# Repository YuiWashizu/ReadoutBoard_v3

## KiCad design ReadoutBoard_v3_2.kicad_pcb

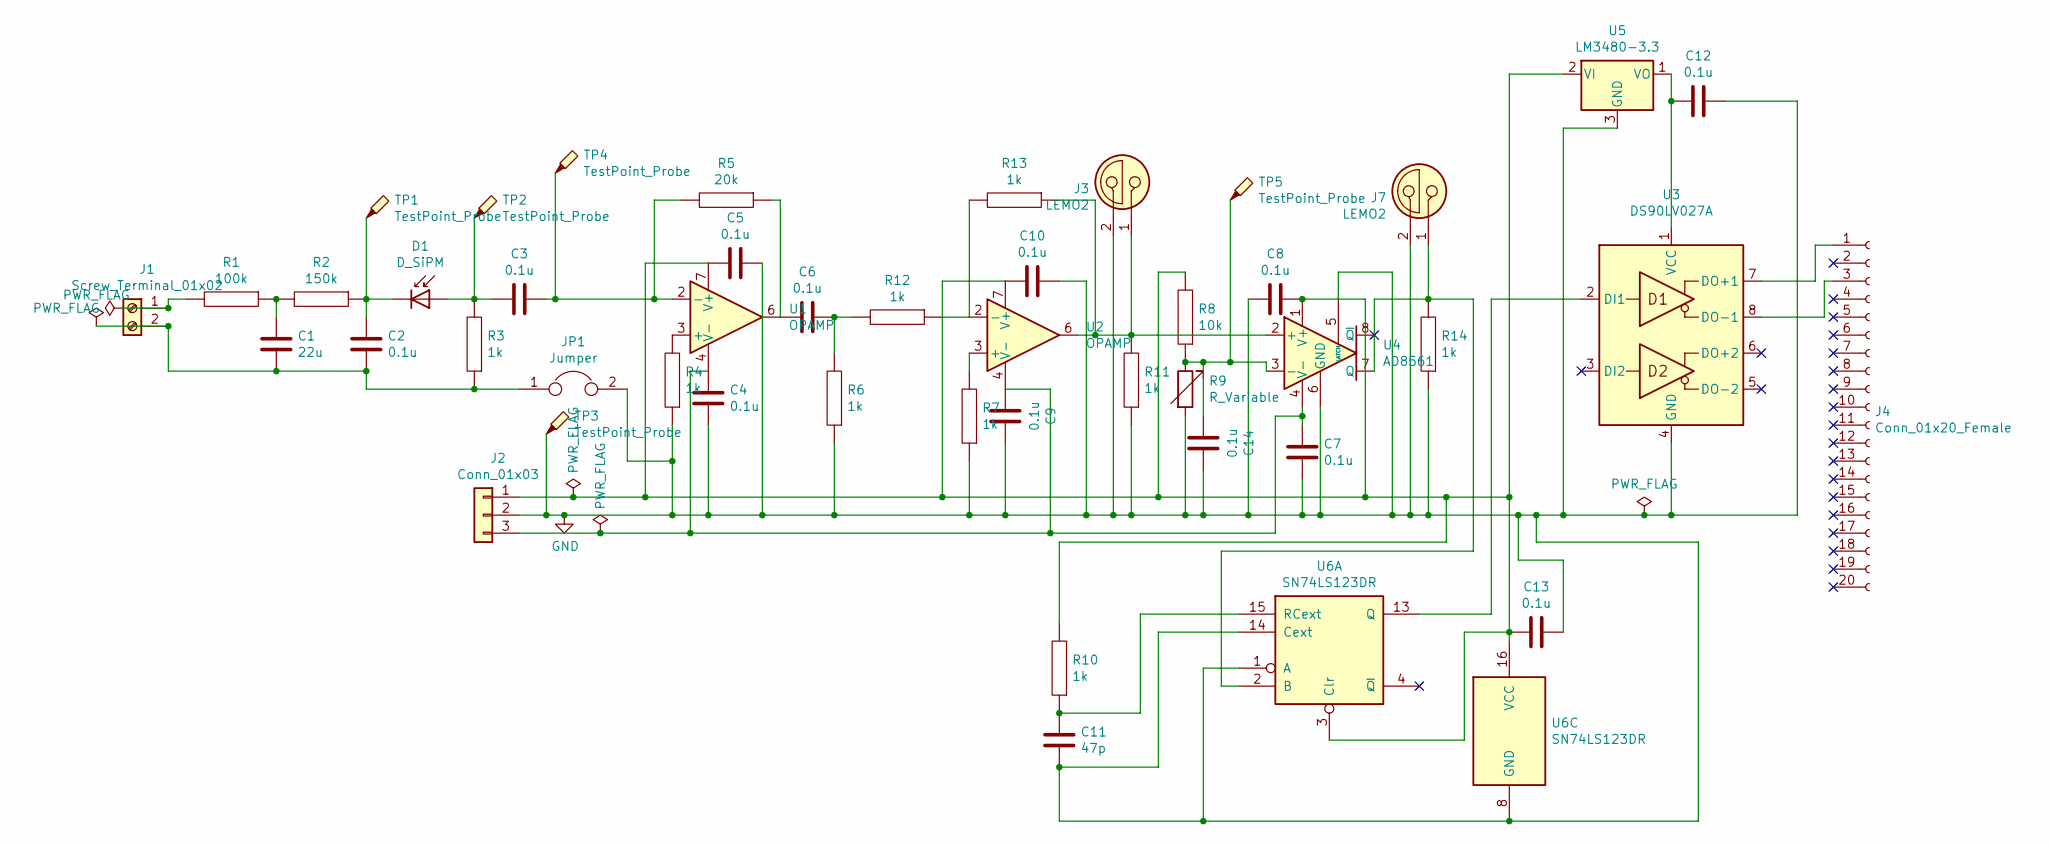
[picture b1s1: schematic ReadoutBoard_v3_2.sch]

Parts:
C1: 22u; PinHeader_1x02_P2.54mm_Vertical
C2, C3, C4, C5, C6, C7, C8, C9, C10, C12, C13, C14: 0.1u; C_0603_1608Metric
C11: 47p; C_0603_1608Metric
D1: D_SiPM; PinHeader_1x02_P2.54mm_Vertical
J1: Screw_Terminal_01x02; TerminalBlock_bornier-2_P5.08mm
J2: Conn_01x03; FanPinHeader_1x03_P2.54mm_Vertical
J3, J7: LEMO2; SMA_Amphenol_132134-16_Vertical
J4: Conn_01x20_Female; DisplayPort
JP1: Jumper; PinHeader_1x02_P2.54mm_Vertical
R1: 100k; R_0402_1005Metric
R2: 150k; R_0402_1005Metric
R3, R4, R6, R7, R10, R11, R12, R13, R14: 1k; R_0402_1005Metric
R5: 20k; R_0402_1005Metric
R8: 10k; R_0402_1005Metric
R9: R_Variable; PinHeader_1x03_P2.54mm_Vertical
TP1, TP2, TP3, TP4, TP5: TestPoint_Probe; TestPoint_Loop_D2.50mm_Drill1.0mm
U1, U2: OPAMP; SOIC-8_3.9x4.9mm_P1.27mm
U3: DS90LV027A; SOIC-8_3.9x4.9mm_P1.27mm
U4: AD8561; SOIC-8_3.9x4.9mm_P1.27mm
U5: LM3480-3.3; SOT-23
U6: SN74LS123DR; SOIC-16_3.9x9.9mm_P1.27mm

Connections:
GND: C4.1, C5.1, C7.1, C8.2, C9.1, C10.1, C11.1, C12.1, C13.1, C14.1, J2.2, J3.2, J7.2, JP1.2, R4.1, R6.1, R7.1, R9.2, R11.1, R14.1, TP3.1, U3.4 (GND), U4.5 (LATCH), U4.6 (GND), U5.3 (GND), U6.1 (A), U6.8 (GND), U6.14 (Cext)
unnamed: C1.1, R1.1, R2.2
unnamed: C1.2, C2.2, J1.2, JP1.1, R3.1
unnamed: C2.1, D1.1 (K), R2.1, TP1.1
unnamed: C3.1, R5.2, TP4.1, U1.2 (-)
unnamed: C3.2, D1.2 (A), R3.2, TP2.1
unnamed: C4.2, C7.2, C9.2, J2.3, U1.4 (V-), U2.4 (V-), U4.4 (V-)
unnamed: C6.1, R6.2, R12.2
unnamed: C6.2, R5.1, U1.6
unnamed: C5.2, C8.1, C10.2, C13.2, J2.1, R8.2, R10.2, U1.7 (V+), U2.7 (V+), U4.1 (V+), U5.2 (VI), U6.3 (Clr), U6.16 (VCC)
unnamed: C11.2, R10.1, U6.15 (RCext)
unnamed: C12.2, U3.1 (VCC), U5.1 (VO)
unnamed: C14.2, R8.1, R9.1, TP5.1, U4.3 (-)
unnamed: J1.1, R1.2
unnamed: J3.1, R11.2, R13.1, U2.6, U4.2 (+)
unnamed: J4.1, U3.7 (DO+1)
unnamed: J4.3, U3.8 (DO-1)
unnamed: J7.1, R14.2, U4.7 (Q), U6.2 (B)
unnamed: R4.2, U1.3 (+)
unnamed: R7.2, U2.3 (+)
unnamed: R12.1, R13.2, U2.2 (-)
unnamed: U3.2 (DI1), U6.13 (Q)

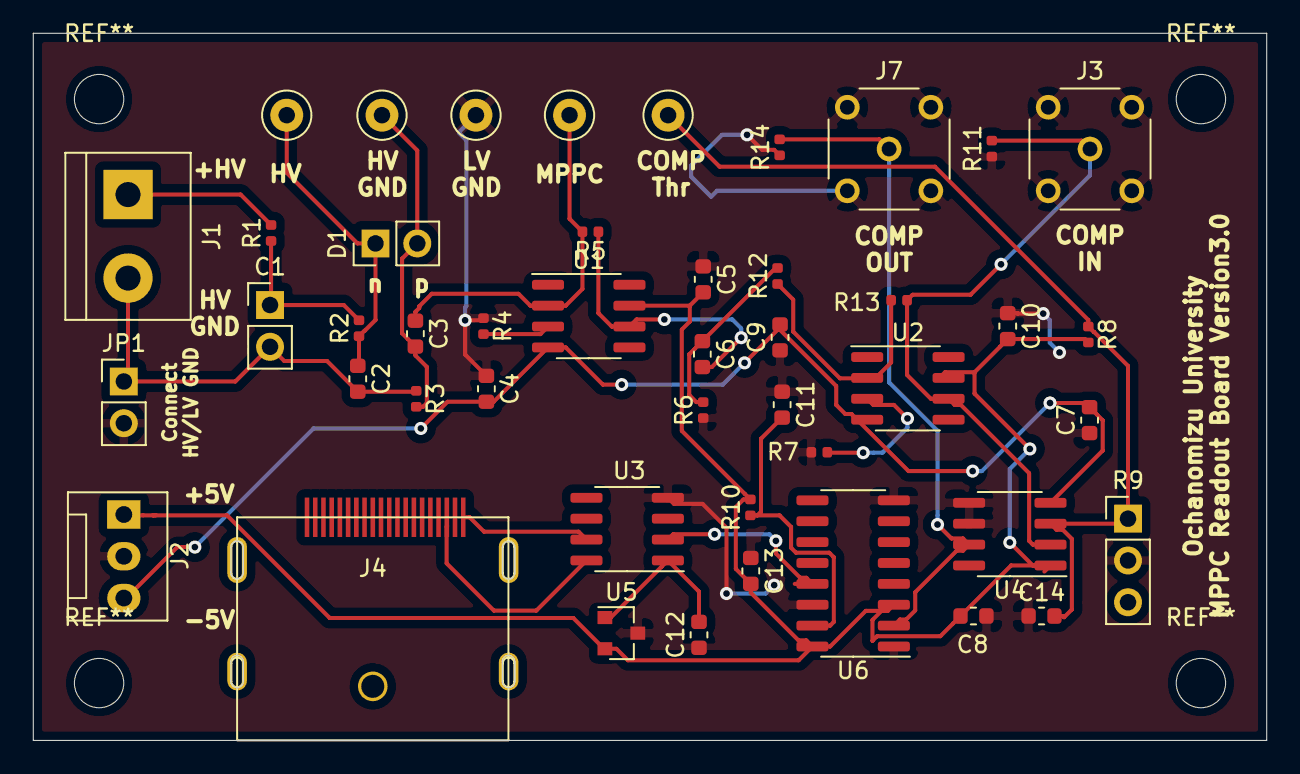
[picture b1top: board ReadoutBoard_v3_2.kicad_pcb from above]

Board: 2 copper layers, 75.0 x 43.0 mm, 46 parts (0 on the bottom side), 22 nets.
